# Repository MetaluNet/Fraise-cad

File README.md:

# Fraise-cad
Fraise-cad is the repo for Fraise boards design files

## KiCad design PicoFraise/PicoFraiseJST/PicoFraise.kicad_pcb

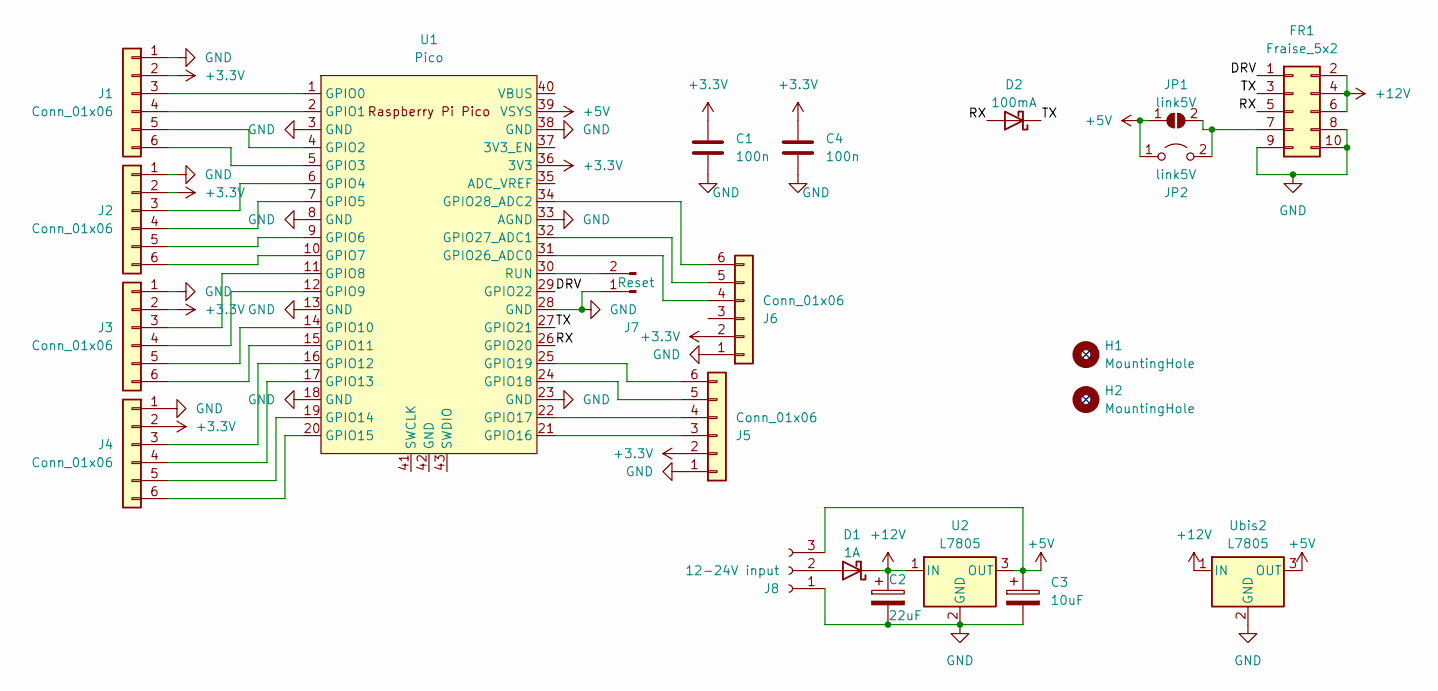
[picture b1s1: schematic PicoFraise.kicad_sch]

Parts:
C1, C4: 100n; C_Rect_L4.0mm_W2.5mm_P2.50mm
C2: 22uF; CP_Radial_D5.0mm_P2.50mm
C3: 10uF; CP_Radial_D5.0mm_P2.50mm
D1: 1A; D_SMA
D2: 100mA; D_SMA
FR1: Fraise_5x2; IDC-Header_2x05_P2.54mm_Vertical
H1, H2: MountingHole; MountingHole_3.2mm_M3_Pad_TopOnly
J1, J2, J3, J4, J5, J6: Conn_01x06; JST_PH_B6B-PH-K_1x06_P2.00mm_Vertical
J7: Reset; PinHeader_1x02_P2.54mm_Vertical
J8: 12-24V input; TerminalBlock_bornier-3_P5.08mm
JP1: link5V; SolderJumper-2_P1.3mm_Open_RoundedPad1.0x1.5mm
JP2: link5V; TestPoint_2Pads_Pitch2.54mm_Drill0.8mm
U1: Pico; RPi_Pico_SMD_TH
U2: L7805; TO-220-3_Vertical
Ubis2: L7805; TO-252-3_TabPin2

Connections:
+3.3V: C1.1, C4.1, J1.2, J2.2, J3.2, J4.2, J5.2, J6.2, U1.36 (3V3)
+5V: C3.1, J8.3, JP1.1 (A), JP2.1 (A), U1.39 (VSYS), U2.3 (OUT), Ubis2.3 (OUT)
+12V: C2.1, D1.1 (K), FR1.2, FR1.4, FR1.6, U2.1 (IN), Ubis2.1 (IN)
/DRV: FR1.1, U1.29 (GPIO22)
/RX: D2.2 (A), FR1.5, U1.26 (GPIO20)
/TX: D2.1 (K), FR1.3, U1.27 (GPIO21)
GND: C1.2, C2.2, C3.2, C4.2, FR1.8, FR1.9, FR1.10, J1.1, J2.1, J3.1, J4.1, J5.1, J6.1, J7.1, J8.1, U1.3 (GND), U1.8 (GND), U1.13 (GND), U1.18 (GND), U1.23 (GND), U1.28 (GND), U1.33 (AGND), U1.38 (GND), U2.2 (GND), Ubis2.2 (GND)
unnamed: D1.2 (A), J8.2
unnamed: FR1.7, JP1.2 (B), JP2.2 (B)
unnamed: J1.3, U1.1 (GPIO0)
unnamed: J1.4, U1.2 (GPIO1)
unnamed: J1.5, U1.4 (GPIO2)
unnamed: J1.6, U1.5 (GPIO3)
unnamed: J2.3, U1.6 (GPIO4)
unnamed: J2.4, U1.7 (GPIO5)
unnamed: J2.5, U1.9 (GPIO6)
unnamed: J2.6, U1.10 (GPIO7)
unnamed: J3.3, U1.11 (GPIO8)
unnamed: J3.4, U1.12 (GPIO9)
unnamed: J3.5, U1.14 (GPIO10)
unnamed: J3.6, U1.15 (GPIO11)
unnamed: J4.3, U1.16 (GPIO12)
unnamed: J4.4, U1.17 (GPIO13)
unnamed: J4.5, U1.19 (GPIO14)
unnamed: J4.6, U1.20 (GPIO15)
unnamed: J5.3, U1.21 (GPIO16)
unnamed: J5.4, U1.22 (GPIO17)
unnamed: J5.5, U1.24 (GPIO18)
unnamed: J5.6, U1.25 (GPIO19)
unnamed: J6.4, U1.31 (GPIO26_ADC0)
unnamed: J6.5, U1.32 (GPIO27_ADC1)
unnamed: J6.6, U1.34 (GPIO28_ADC2)
unnamed: J7.2, U1.30 (RUN)

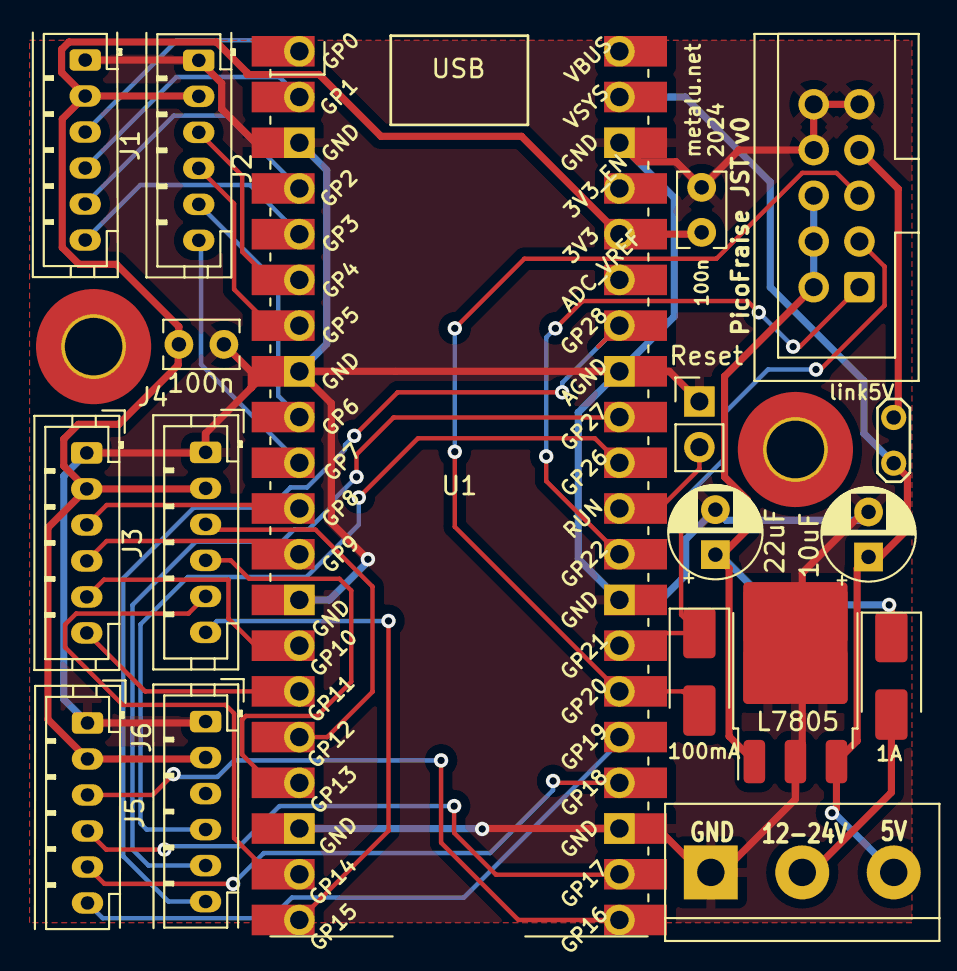
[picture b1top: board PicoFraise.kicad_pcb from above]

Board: 2 copper layers, 21 parts (1 on the bottom side), 33 nets.

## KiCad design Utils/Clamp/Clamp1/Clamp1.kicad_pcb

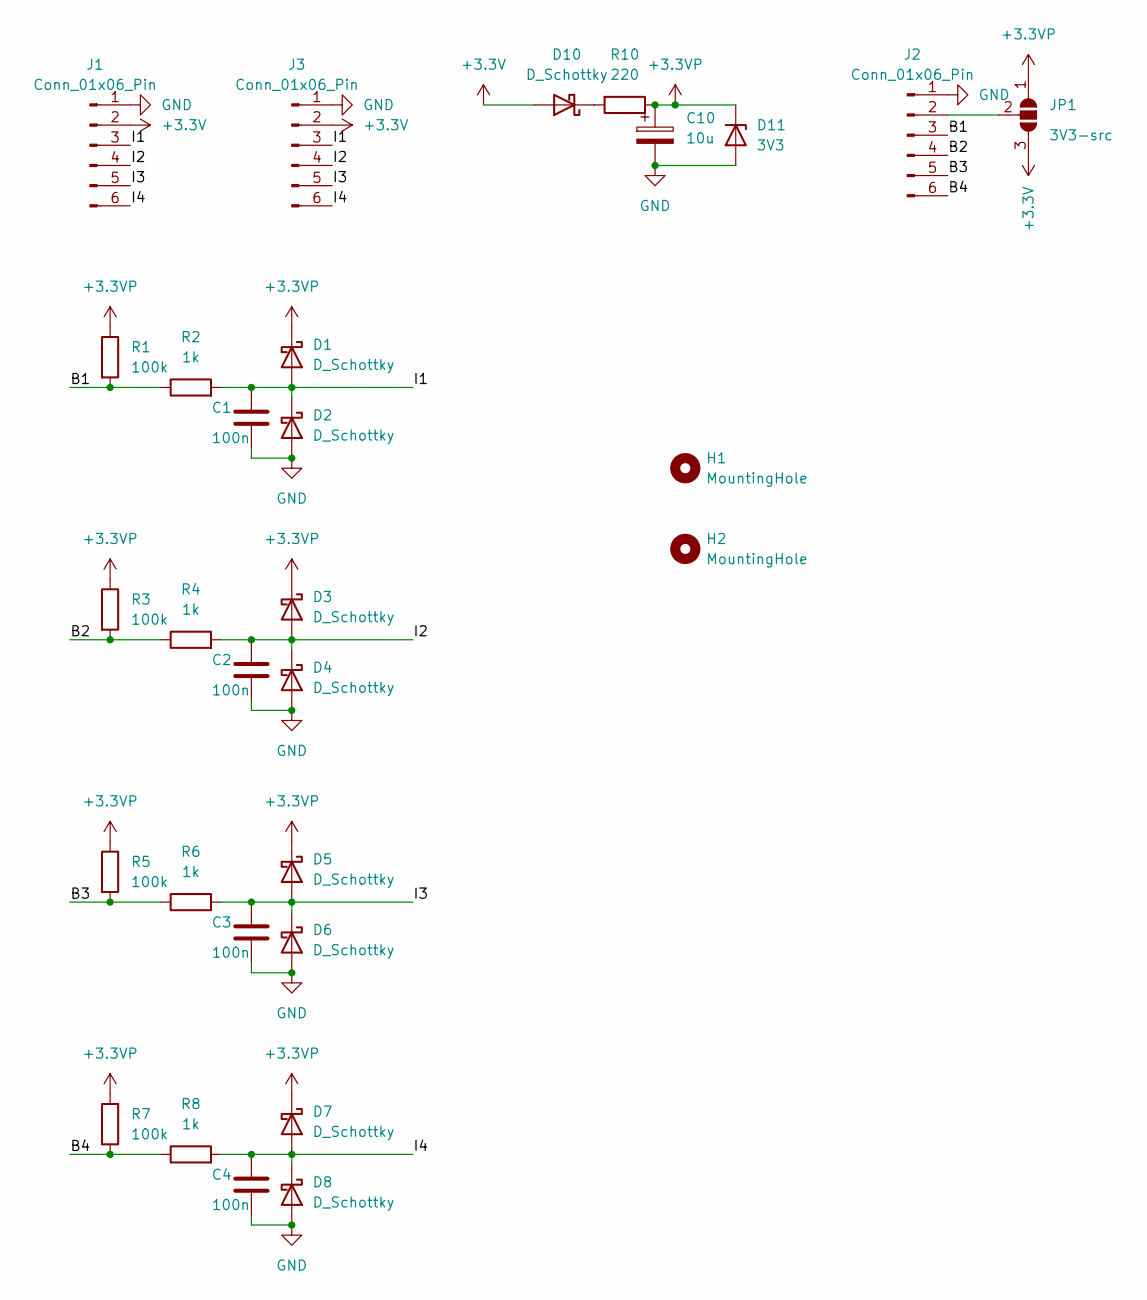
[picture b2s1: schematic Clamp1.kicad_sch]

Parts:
C1, C2, C3, C4: 100n; C_Rect_L4.0mm_W2.5mm_P2.50mm
C10: 10u; CP_Radial_D5.0mm_P2.50mm
D1, D2, D3, D4, D5, D6, D7, D8, D10: D_Schottky; D_DO-41_SOD81_P7.62mm_Horizontal
D11: 3V3; D_DO-41_SOD81_P7.62mm_Horizontal
H1, H2: MountingHole; MountingHole_3.2mm_M3_ISO7380_Pad
J1: Conn_01x06_Pin; Molex_KK-254_AE-6410-06A_1x06_P2.54mm_Vertical
J2: Conn_01x06_Pin; TerminalBlock_bornier-6_P5.08mm
J3: Conn_01x06_Pin; JST_PH_B6B-PH-K_1x06_P2.00mm_Vertical
JP1: 3V3-src; SolderJumper-3_P1.3mm_Open_RoundedPad1.0x1.5mm_NumberLabels
R1, R3, R5, R7: 100k; R_Axial_DIN0207_L6.3mm_D2.5mm_P7.62mm_Horizontal
R2, R4, R6, R8: 1k; R_Axial_DIN0207_L6.3mm_D2.5mm_P7.62mm_Horizontal
R10: 220; R_Axial_DIN0207_L6.3mm_D2.5mm_P7.62mm_Horizontal

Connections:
+3.3V: D10.2 (A), J1.2, J3.2, JP1.3 (B)
+3.3VP: C10.1, D1.1 (K), D3.1 (K), D5.1 (K), D7.1 (K), D11.1 (K), JP1.1 (A), R1.1, R3.1, R5.1, R7.1, R10.1
/B1: J2.3, R1.2, R2.1
/B2: J2.4, R3.2, R4.1
/B3: J2.5, R5.2, R6.1
/B4: J2.6, R7.2, R8.1
/I1: C1.1, D1.2 (A), D2.1 (K), J1.3, J3.3, R2.2
/I2: C2.1, D3.2 (A), D4.1 (K), J1.4, J3.4, R4.2
/I3: C3.1, D5.2 (A), D6.1 (K), J1.5, J3.5, R6.2
/I4: C4.1, D7.2 (A), D8.1 (K), J1.6, J3.6, R8.2
GND: C1.2, C2.2, C3.2, C4.2, C10.2, D2.2 (A), D4.2 (A), D6.2 (A), D8.2 (A), D11.2 (A), J1.1, J2.1, J3.1
unnamed: D10.1 (K), R10.2
unnamed: J2.2, JP1.2 (C)

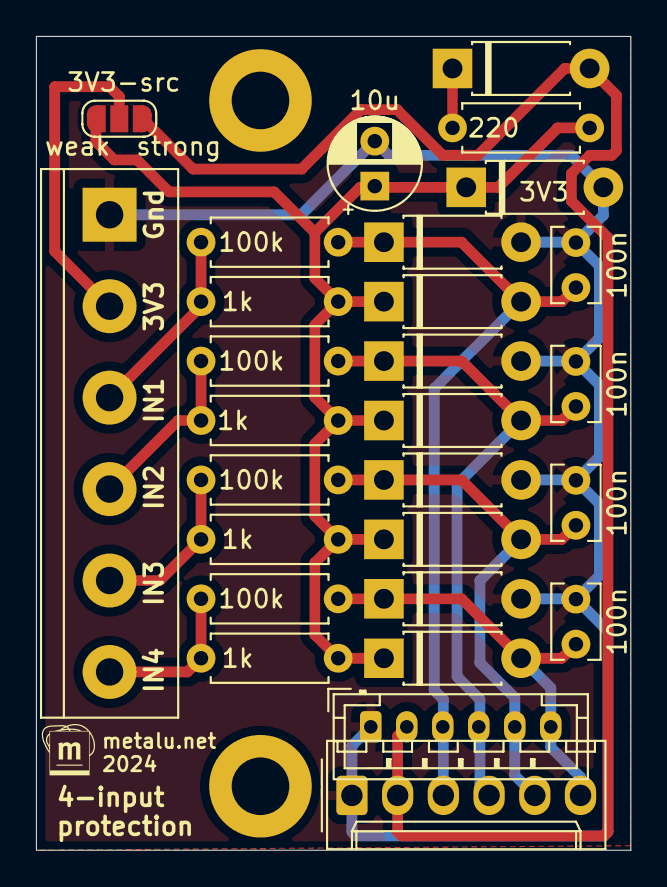
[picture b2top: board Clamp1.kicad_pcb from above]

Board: 2 copper layers, 33.0 x 45.2 mm, 30 parts (0 on the bottom side), 13 nets.

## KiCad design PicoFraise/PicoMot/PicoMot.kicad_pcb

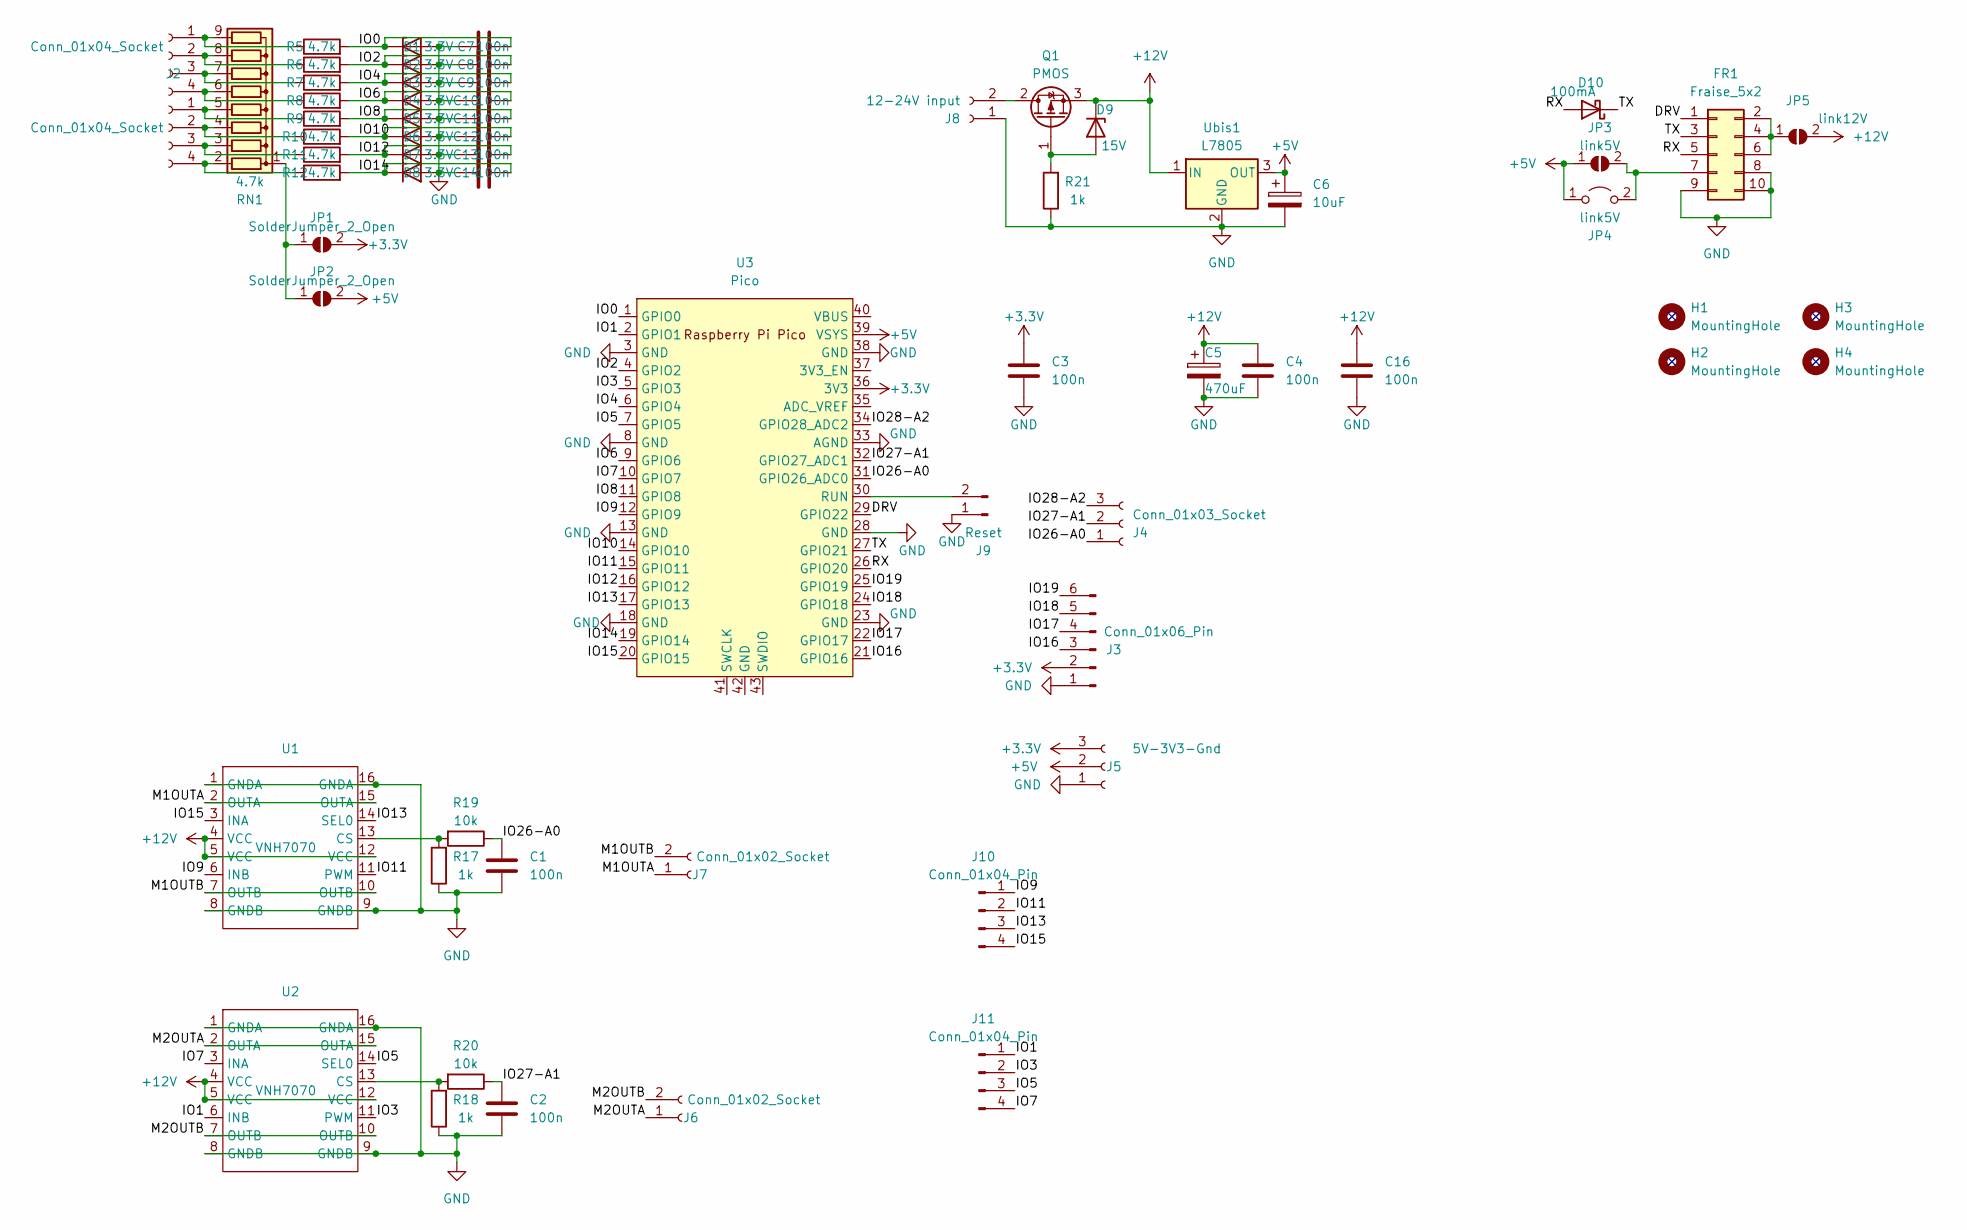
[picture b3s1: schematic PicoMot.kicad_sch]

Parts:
C1, C2, C3, C4, C7, C8, C9, C10, C11, C12, C13, C14, C16: 100n; C_Rect_L4.0mm_W2.5mm_P2.50mm
C5: 470uF; CP_Radial_D10.0mm_P5.00mm
C6: 10uF; CP_Radial_D5.0mm_P2.50mm
D1, D2, D3, D4, D5, D6, D7, D8: 3.3V; D_A-405_P2.54mm_Vertical_KathodeUp
D9: 15V; D_A-405_P2.54mm_Vertical_KathodeUp
D10: 100mA; D_SMA
FR1: Fraise_5x2; IDC-Header_2x05_P2.54mm_Vertical
H1, H2, H3, H4: MountingHole; MountingHole_3.2mm_M3_Pad_TopOnly
J1, J2: Conn_01x04_Socket; TerminalBlock_bornier-4_P5.08mm
J3: Conn_01x06_Pin; Molex_KK-254_AE-6410-06A_1x06_P2.54mm_Vertical
J4: Conn_01x03_Socket; Molex_KK-254_AE-6410-03A_1x03_P2.54mm_Vertical
J5: 5V-3V3-Gnd; TerminalBlock_bornier-3_P5.08mm
J6, J7: Conn_01x02_Socket; TerminalBlock_bornier-2_P5.08mm
J8: 12-24V input; TerminalBlock_bornier-2_P5.08mm
J9: Reset; PinHeader_1x02_P2.54mm_Vertical
J10, J11: Conn_01x04_Pin; Molex_KK-254_AE-6410-04A_1x04_P2.54mm_Vertical
JP1, JP2: SolderJumper_2_Open; SolderJumper-2_P1.3mm_Open_RoundedPad1.0x1.5mm
JP3: link5V; SolderJumper-2_P1.3mm_Open_RoundedPad1.0x1.5mm
JP4: link5V; TestPoint_2Pads_Pitch2.54mm_Drill0.8mm
JP5: link12V; SolderJumper-2_P1.3mm_Open_RoundedPad1.0x1.5mm
Q1: PMOS; TO-252-3_TabPin2
R5, R6, R7, R8, R9, R10, R11, R12: 4.7k; R_Axial_DIN0204_L3.6mm_D1.6mm_P2.54mm_Vertical
R17, R18, R21: 1k; R_Axial_DIN0204_L3.6mm_D1.6mm_P7.62mm_Horizontal
R19, R20: 10k; R_Axial_DIN0204_L3.6mm_D1.6mm_P7.62mm_Horizontal
RN1: 4.7k; R_Array_SIP9
U1, U2: VNH7070; SOIC-16_3.9x9.9mm_P1.27mm
U3: Pico; RPi_Pico_SMD_TH
Ubis1: L7805; TO-252-3_TabPin2

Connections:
+3.3V: C3.1, J3.2, J5.3, JP1.2 (B), U3.36 (3V3)
+5V: C6.1, J5.2, JP2.2 (B), JP3.1 (A), JP4.1 (A), U3.39 (VSYS), Ubis1.3 (OUT)
+12V: C4.1, C5.1, C16.1, D9.1 (K), JP5.2 (B), Q1.3 (S), U1.4 (VCC), U1.5 (VCC), U1.12 (VCC), U2.4 (VCC), U2.5 (VCC), U2.12 (VCC), Ubis1.1 (IN)
/DRV: FR1.1, U3.29 (GPIO22)
/IO0: C7.2, D1.1 (K), R5.2, U3.1 (GPIO0)
/IO1: J11.1, U2.6 (INB), U3.2 (GPIO1)
/IO2: C8.2, D2.1 (K), R6.2, U3.4 (GPIO2)
/IO3: J11.2, U2.11 (PWM), U3.5 (GPIO3)
/IO4: C9.2, D3.1 (K), R7.2, U3.6 (GPIO4)
/IO5: J11.3, U2.14 (SEL0), U3.7 (GPIO5)
/IO6: C10.2, D4.1 (K), R8.2, U3.9 (GPIO6)
/IO7: J11.4, U2.3 (INA), U3.10 (GPIO7)
/IO8: C11.2, D5.1 (K), R9.2, U3.11 (GPIO8)
/IO9: J10.1, U1.6 (INB), U3.12 (GPIO9)
/IO10: C12.2, D6.1 (K), R10.2, U3.14 (GPIO10)
/IO11: J10.2, U1.11 (PWM), U3.15 (GPIO11)
/IO12: C13.2, D7.1 (K), R11.2, U3.16 (GPIO12)
/IO13: J10.3, U1.14 (SEL0), U3.17 (GPIO13)
/IO14: C14.2, D8.1 (K), R12.2, U3.19 (GPIO14)
/IO15: J10.4, U1.3 (INA), U3.20 (GPIO15)
/IO16: J3.3, U3.21 (GPIO16)
/IO17: J3.4, U3.22 (GPIO17)
/IO18: J3.5, U3.24 (GPIO18)
/IO19: J3.6, U3.25 (GPIO19)
/IO26-A0: C1.1, J4.1, R19.1, U3.31 (GPIO26_ADC0)
/IO27-A1: C2.1, J4.2, R20.1, U3.32 (GPIO27_ADC1)
/IO28-A2: J4.3, U3.34 (GPIO28_ADC2)
/M1OUTA: J7.1, U1.2 (OUTA), U1.15 (OUTA)
/M1OUTB: J7.2, U1.7 (OUTB), U1.10 (OUTB)
/M2OUTA: J6.1, U2.2 (OUTA), U2.15 (OUTA)
/M2OUTB: J6.2, U2.7 (OUTB), U2.10 (OUTB)
/RX: D10.2 (A), FR1.5, U3.26 (GPIO20)
/TX: D10.1 (K), FR1.3, U3.27 (GPIO21)
GND: C1.2, C2.2, C3.2, C4.2, C5.2, C6.2, C7.1, C8.1, C9.1, C10.1, C11.1, C12.1, C13.1, C14.1, C16.2, D1.2 (A), D2.2 (A), D3.2 (A), D4.2 (A), D5.2 (A), D6.2 (A), D7.2 (A), D8.2 (A), FR1.8, FR1.9, FR1.10, J3.1, J5.1, J8.1, J9.1, R17.1, R18.1, R21.1, U1.1 (GNDA), U1.8 (GNDB), U1.9 (GNDB), U1.16 (GNDA), U2.1 (GNDA), U2.8 (GNDB), U2.9 (GNDB), U2.16 (GNDA), U3.3 (GND), U3.8 (GND), U3.13 (GND), U3.18 (GND), U3.23 (GND), U3.28 (GND), U3.33 (AGND), U3.38 (GND), Ubis1.2 (GND)
unnamed: D9.2 (A), Q1.1 (G), R21.2
unnamed: FR1.2, FR1.4, FR1.6, JP5.1 (A)
unnamed: FR1.7, JP3.2 (B), JP4.2 (B)
unnamed: J1.1, R5.1, RN1.9 (R8)
unnamed: J1.2, R6.1, RN1.8 (R7)
unnamed: J1.3, R7.1, RN1.7 (R6)
unnamed: J1.4, R8.1, RN1.6 (R5)
unnamed: J2.1, R9.1, RN1.5 (R4)
unnamed: J2.2, R10.1, RN1.4 (R3)
unnamed: J2.3, R11.1, RN1.3 (R2)
unnamed: J2.4, R12.1, RN1.2 (R1)
unnamed: J8.2, Q1.2 (D)
unnamed: J9.2, U3.30 (RUN)
unnamed: JP1.1 (A), JP2.1 (A), RN1.1 (common)
unnamed: R17.2, R19.2, U1.13 (CS)
unnamed: R18.2, R20.2, U2.13 (CS)

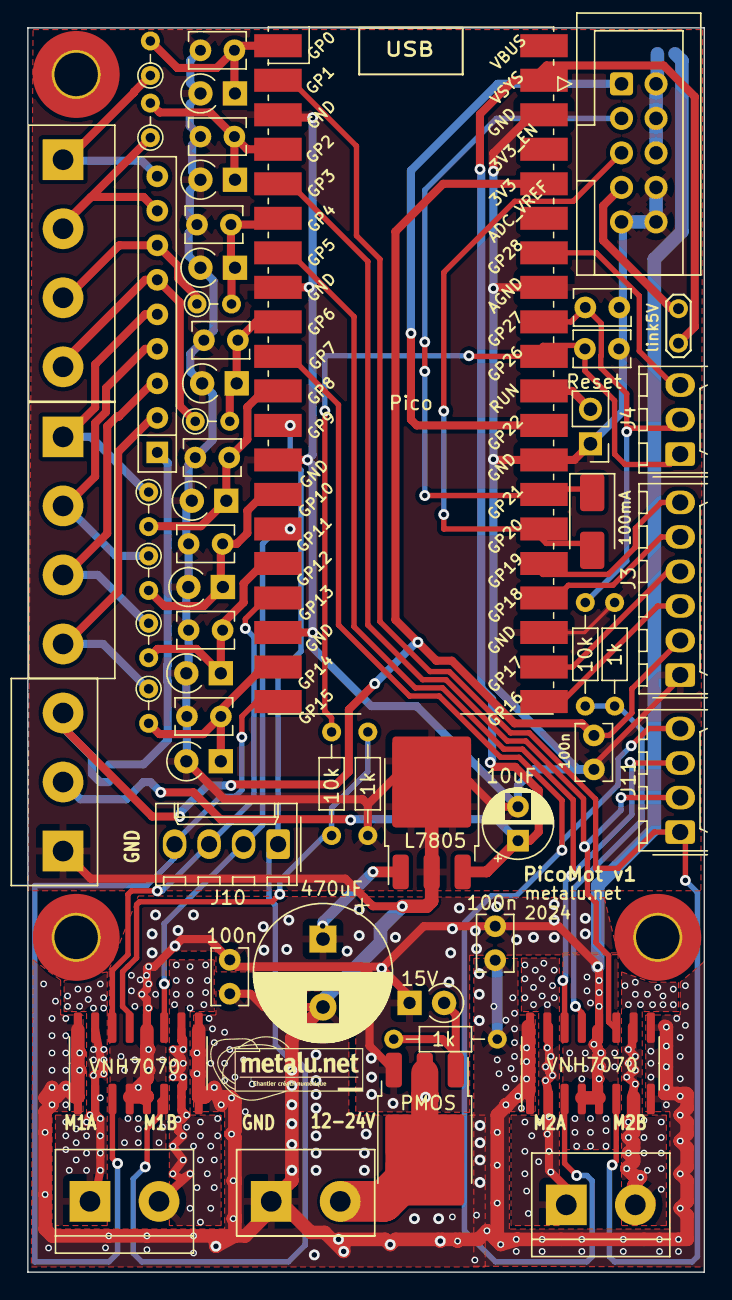
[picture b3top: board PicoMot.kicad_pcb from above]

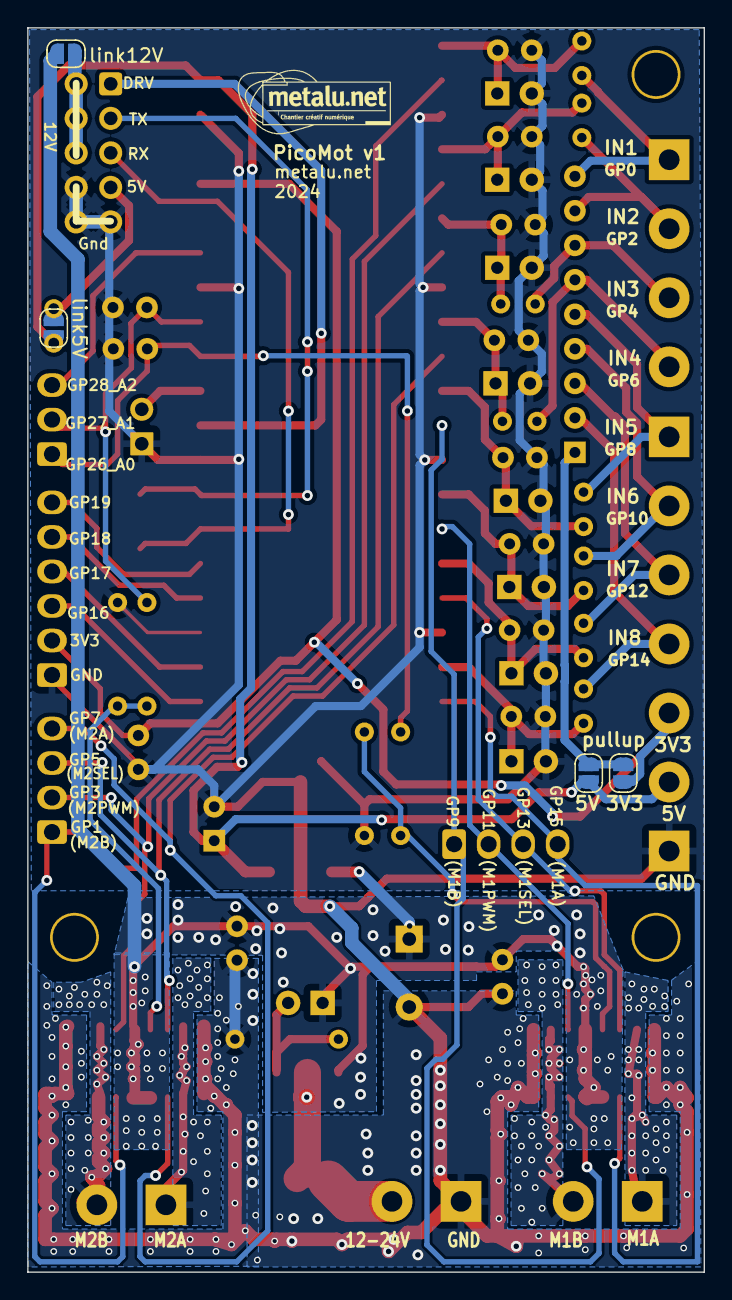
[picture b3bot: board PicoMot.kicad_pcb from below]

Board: 2 copper layers, 49.8 x 91.6 mm, 64 parts (4 on the bottom side), 50 nets.

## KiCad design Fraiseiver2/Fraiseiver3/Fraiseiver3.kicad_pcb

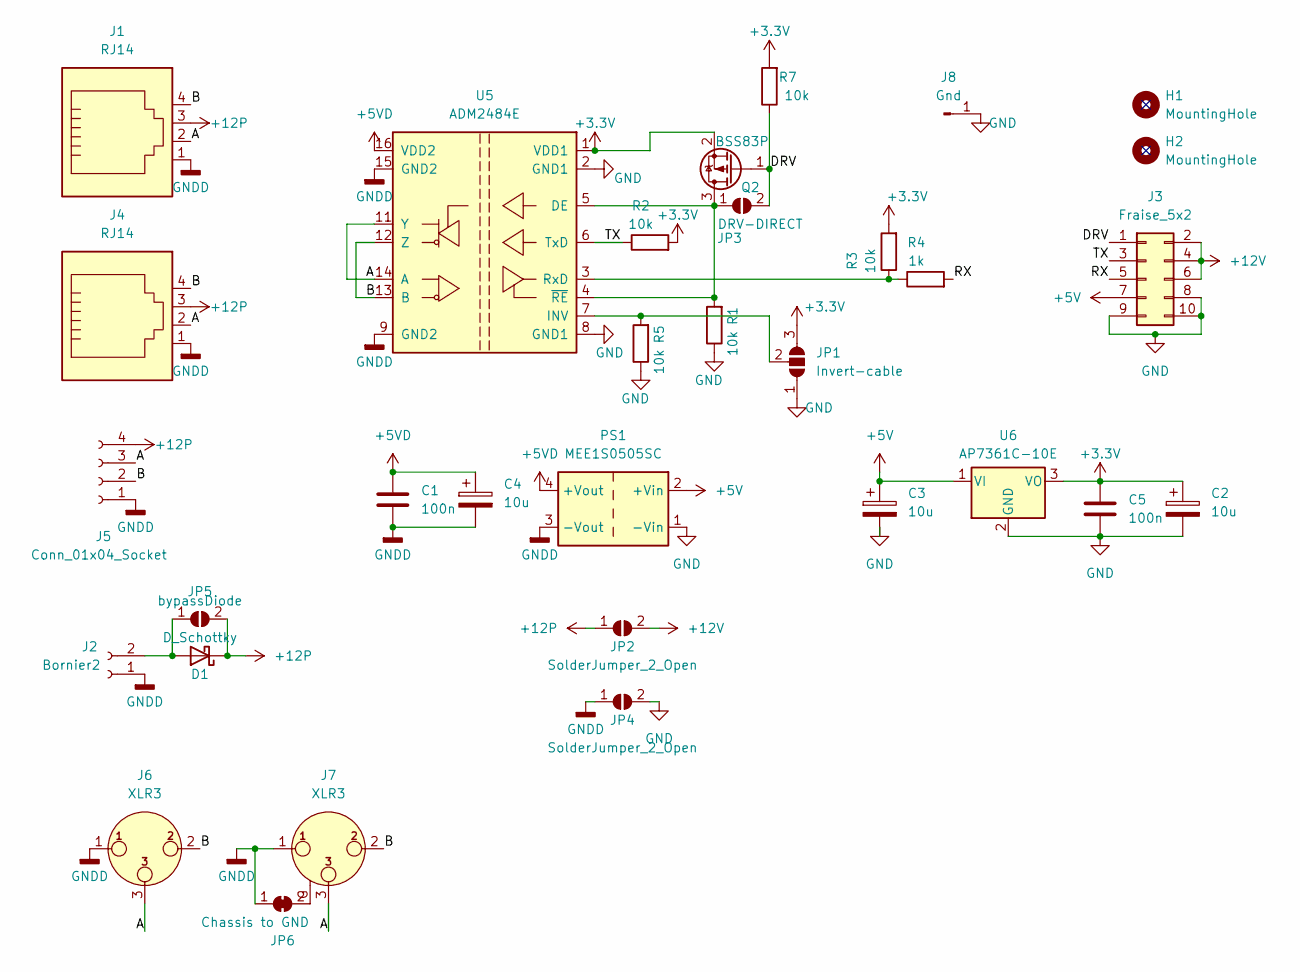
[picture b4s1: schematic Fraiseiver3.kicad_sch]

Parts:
C1, C5: 100n; C_Rect_L4.6mm_W2.0mm_P2.50mm_MKS02_FKP02
C2, C3, C4: 10u; CP_Radial_D5.0mm_P2.50mm
D1: D_Schottky; D_SMA
H1, H2: MountingHole; MountingHole_3.2mm_M3_Pad_TopOnly
J1, J4: RJ14; RJ11
J2: Bornier2; TerminalBlock_Phoenix_MKDS-3-2-5.08_1x02_P5.08mm_Horizontal
J3: Fraise_5x2; IDC-Header_2x05_P2.54mm_Vertical
J5: Conn_01x04_Socket; TerminalBlock_bornier-4_P5.08mm
J6: XLR3; Jack_XLR_Neutrik_NC3FAAH-0_Horizontal
J7: XLR3; Jack_XLR_Neutrik_NC3MAAH-1_Horizontal
J8: Gnd; PinHeader_1x01_P2.54mm_Vertical
JP1: Invert-cable; SolderJumper-3_P1.3mm_Open_RoundedPad1.0x1.5mm_NumberLabels
JP2, JP4: SolderJumper_2_Open; SolderJumper-2_P1.3mm_Open_RoundedPad1.0x1.5mm
JP3: DRV-DIRECT; SolderJumper-2_P1.3mm_Open_RoundedPad1.0x1.5mm
JP5: bypassDiode; SolderJumper-2_P1.3mm_Open_RoundedPad1.0x1.5mm
JP6: Chassis to GND; SolderJumper-2_P1.3mm_Bridged_RoundedPad1.0x1.5mm
PS1: MEE1S0505SC; Converter_DCDC_Murata_MEE1SxxxxSC_THT
Q2: BSS83P; SOT-23
R1, R2, R3, R5, R7: 10k; R_Axial_DIN0204_L3.6mm_D1.6mm_P5.08mm_Horizontal
R4: 1k; R_Axial_DIN0204_L3.6mm_D1.6mm_P5.08mm_Horizontal
U5: ADM2484E; SOIC-16W_7.5x10.3mm_P1.27mm
U6: AP7361C-10E; SOT-223-3_TabPin2

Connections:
+3.3V: C2.1, C5.1, JP1.3 (B), Q2.2 (S), R2.2, R3.2, R7.2, U5.1 (VDD1), U6.3 (VO)
+5V: C3.1, J3.7, PS1.2 (+Vin), U6.1 (VI)
+5VD: C1.1, C4.1, PS1.4 (+Vout), U5.16 (VDD2)
+12P: D1.1 (K), J1.3, J4.3, J5.4, JP2.1 (A), JP5.2 (B)
+12V: J3.2, J3.4, J3.6, JP2.2 (B)
/A: J1.2, J4.2, J5.3, J6.3, J7.3, U5.11 (Y), U5.14 (A)
/B: J1.4, J4.4, J5.2, J6.2, J7.2, U5.12 (Z), U5.13 (B)
/DRV: J3.1, JP3.2 (B), Q2.1 (G), R7.1
/RX: J3.5, R4.2
/TX: J3.3, R2.1, U5.6 (TxD)
GND: C2.2, C3.2, C5.2, J3.8, J3.9, J3.10, J8.1, JP1.1 (A), JP4.2 (B), PS1.1 (-Vin), R1.1, R5.1, U5.2 (GND1), U5.8 (GND1), U6.2 (GND)
GNDD: C1.2, C4.2, J1.1, J2.1, J4.1, J5.1, J6.1, J7.1, JP4.1 (A), JP6.1 (A), PS1.3 (-Vout), U5.9 (GND2), U5.15 (GND2)
unnamed: D1.2 (A), J2.2, JP5.1 (A)
unnamed: JP1.2 (C), R5.2, U5.7 (INV)
unnamed: JP3.1 (A), Q2.3 (D), R1.2, U5.4 (~RE), U5.5 (DE)
unnamed: J7.G, JP6.2 (B)
unnamed: R3.1, R4.1, U5.3 (RxD)

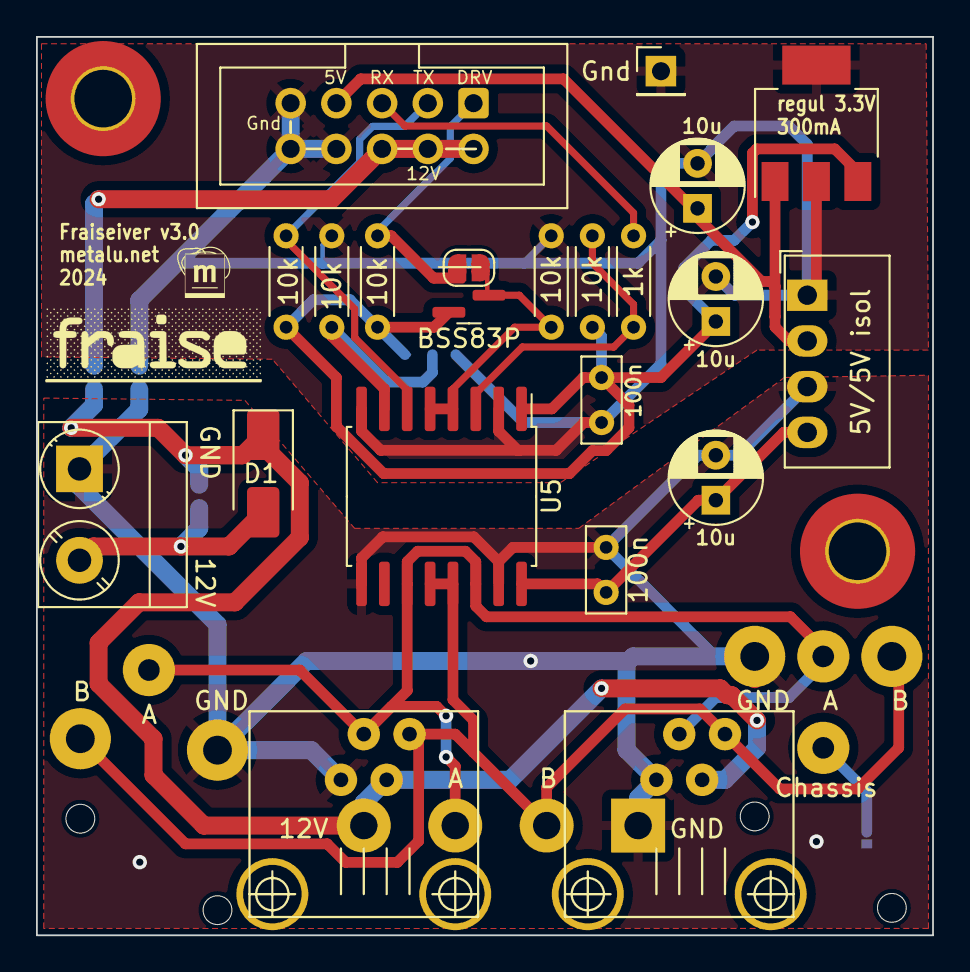
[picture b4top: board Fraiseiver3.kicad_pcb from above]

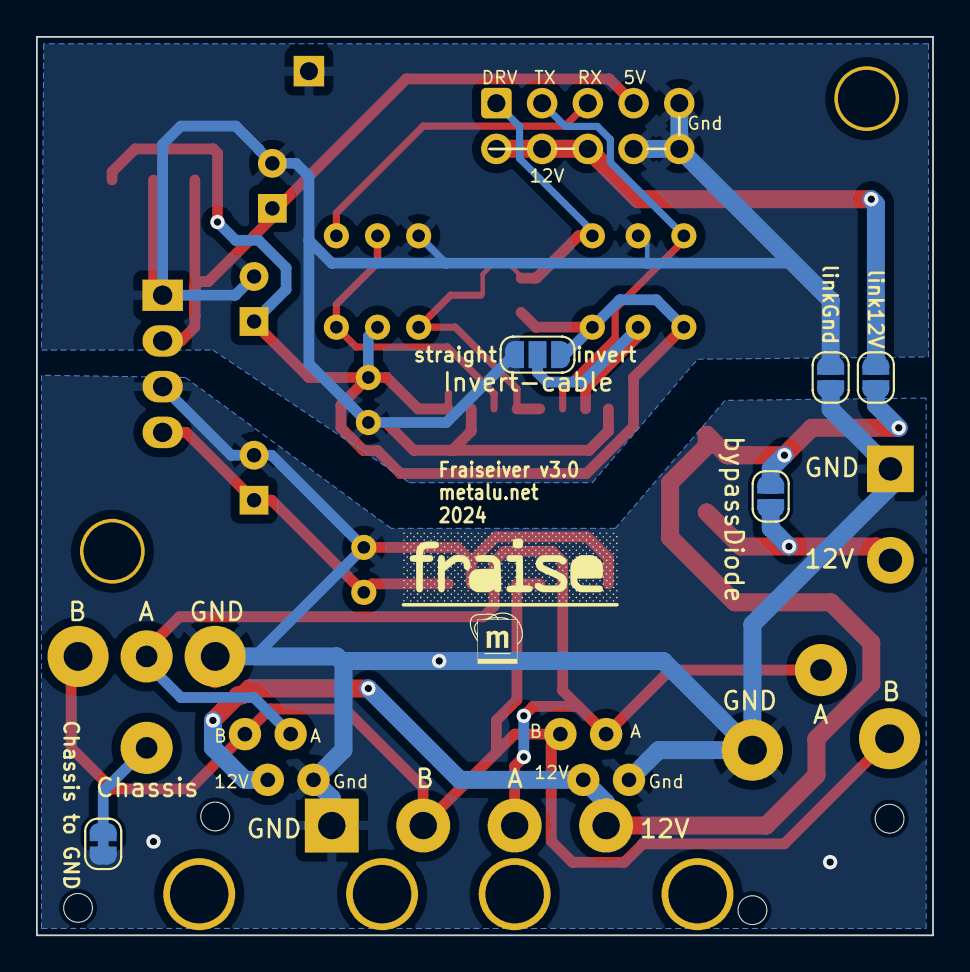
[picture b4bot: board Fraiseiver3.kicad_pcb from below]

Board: 2 copper layers, 49.8 x 49.9 mm, 32 parts (5 on the bottom side), 17 nets.

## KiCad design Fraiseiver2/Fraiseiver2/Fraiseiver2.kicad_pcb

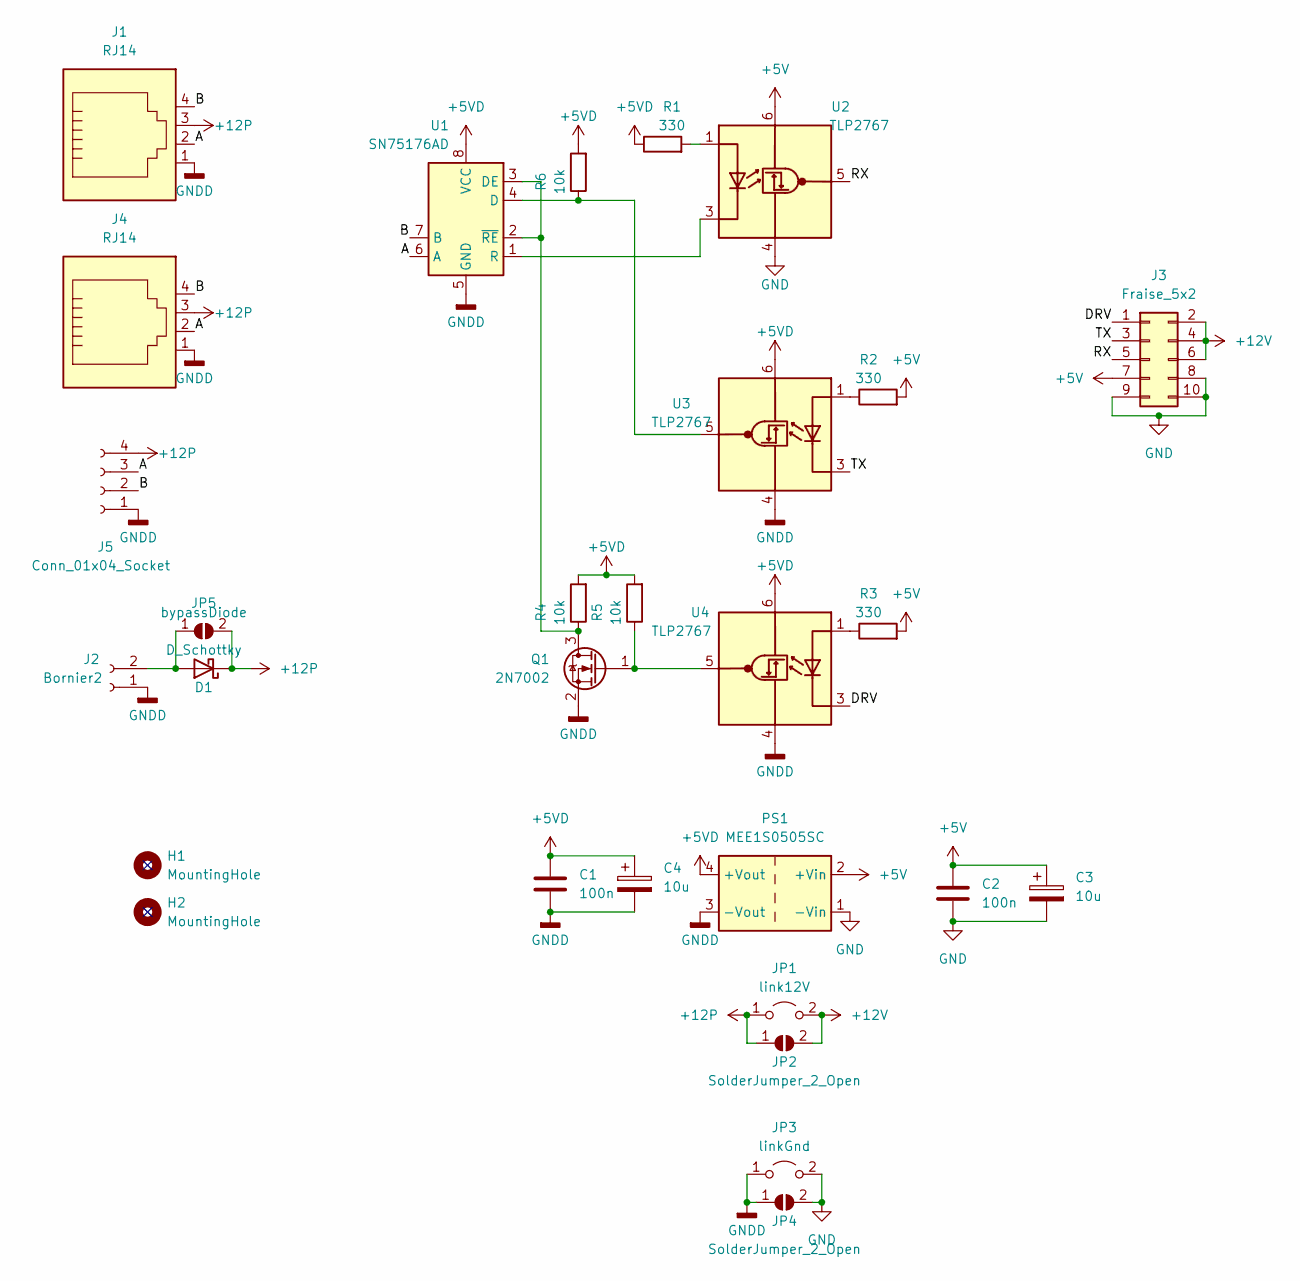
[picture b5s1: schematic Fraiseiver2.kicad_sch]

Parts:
C1, C2: 100n; C_Rect_L4.6mm_W2.0mm_P2.50mm_MKS02_FKP02
C3, C4: 10u; CP_Radial_D5.0mm_P2.50mm
D1: D_Schottky; D_SMA
H1, H2: MountingHole; MountingHole_3.2mm_M3_Pad_TopOnly
J1, J4: RJ14; RJ11
J2: Bornier2; TerminalBlock_Phoenix_MKDS-3-2-5.08_1x02_P5.08mm_Horizontal
J3: Fraise_5x2; IDC-Header_2x05_P2.54mm_Vertical
J5: Conn_01x04_Socket; TerminalBlock_bornier-4_P5.08mm
JP1: link12V; TestPoint_2Pads_Pitch2.54mm_Drill0.8mm
JP2, JP4: SolderJumper_2_Open; SolderJumper-2_P1.3mm_Open_RoundedPad1.0x1.5mm
JP3: linkGnd; TestPoint_2Pads_Pitch2.54mm_Drill0.8mm
JP5: bypassDiode; SolderJumper-2_P1.3mm_Open_RoundedPad1.0x1.5mm
PS1: MEE1S0505SC; Converter_DCDC_Murata_MEE1SxxxxSC_THT
Q1: 2N7002; SOT-23
R1, R2, R3: 330; R_Axial_DIN0204_L3.6mm_D1.6mm_P5.08mm_Horizontal
R4, R5, R6: 10k; R_Axial_DIN0204_L3.6mm_D1.6mm_P5.08mm_Horizontal
U1: SN75176AD; SOIC-8_3.9x4.9mm_P1.27mm
U2, U3, U4: TLP2767; SO-6L_10x3.84mm_P1.27mm

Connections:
+5V: C2.1, C3.1, J3.7, PS1.2 (+Vin), R2.2, R3.2, U2.6 (VDD)
+5VD: C1.1, C4.1, PS1.4 (+Vout), R1.1, R4.2, R5.2, R6.2, U1.8 (VCC), U3.6 (VDD), U4.6 (VDD)
+12P: D1.1 (K), J1.3, J4.3, J5.4, JP1.1 (A), JP2.1 (A), JP5.2 (B)
+12V: J3.2, J3.4, J3.6, JP1.2 (B), JP2.2 (B)
/A: J1.2, J4.2, J5.3, U1.6 (A)
/B: J1.4, J4.4, J5.2, U1.7 (B)
/DRV: J3.1, U4.3 (K)
/RX: J3.5, U2.5 (VO)
/TX: J3.3, U3.3 (K)
GND: C2.2, C3.2, J3.8, J3.9, J3.10, JP3.2 (B), JP4.2 (B), PS1.1 (-Vin), U2.4 (GND)
GNDD: C1.2, C4.2, J1.1, J2.1, J4.1, J5.1, JP3.1 (A), JP4.1 (A), PS1.3 (-Vout), Q1.2 (S), U1.5 (GND), U3.4 (GND), U4.4 (GND)
unnamed: D1.2 (A), J2.2, JP5.1 (A)
unnamed: Q1.3 (D), R4.1, U1.2 (~RE), U1.3 (DE)
unnamed: Q1.1 (G), R5.1, U4.5 (VO)
unnamed: R6.1, U1.4 (D), U3.5 (VO)
unnamed: U1.1 (R), U2.3 (K)
unnamed: R1.2, U2.1 (A)
unnamed: R2.1, U3.1 (A)
unnamed: R3.1, U4.1 (A)

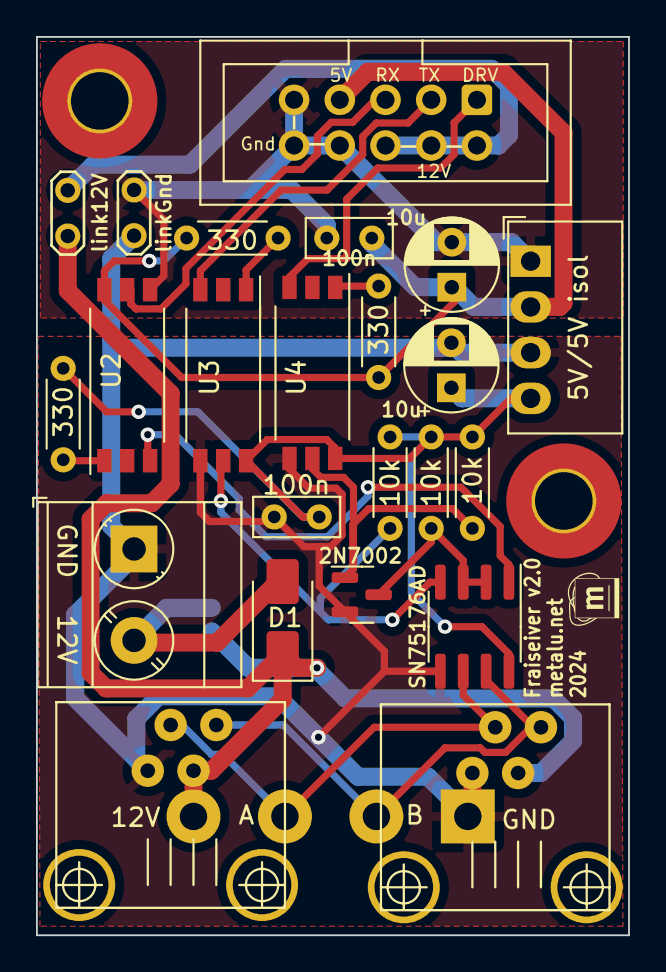
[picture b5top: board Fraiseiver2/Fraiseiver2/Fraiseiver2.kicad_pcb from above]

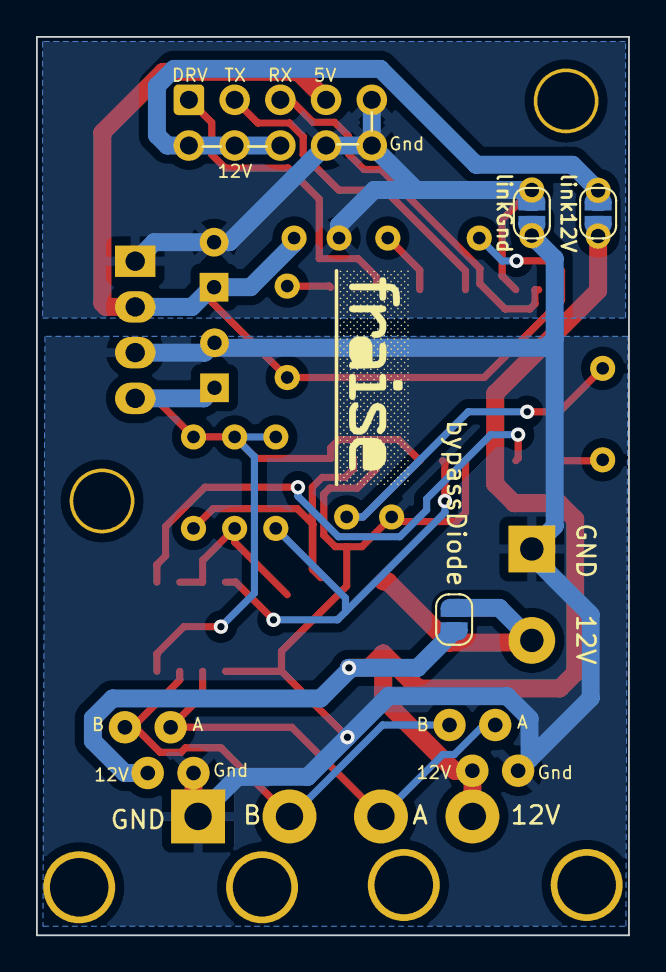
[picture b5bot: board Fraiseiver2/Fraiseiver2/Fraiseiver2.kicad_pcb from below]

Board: 2 copper layers, 32.9 x 49.9 mm, 29 parts (3 on the bottom side), 19 nets.
